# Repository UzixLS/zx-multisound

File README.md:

## ZX-MultiSound
Sound card for ZX Spectrum (NemoBus).

### Tech specs
* TurboSound FM (2xYM2203)
* General Sound (16MHz, 1024Kb of RAM)
* SAA1099 (use port #FF/#1FF to access SAA chip, write #F7/#FF to #FFFD port to enable/disable SAA)
* SounDrive (ports #0F, #1F, #4F, #5F)
* MIDI synthesizer (controlled via YM(AY) chip - compatible with ZX Spectrum 128K / ZXUNO)
* Low profile PCB: 170x64mm
* 5V and 12V power required
* 4x 1-bit digital DACs for GS and SounDrive

### Changelog & current status
* Rev.A - first release. Please note the [errata](pcb/rev.A/ERRATA.txt);
* Rev.A1 - fixed known rev.A issues. Please note the [errata](pcb/rev.A1/ERRATA.txt).
* Rev.A2:
    * Fixed Z80 clocking - added buffer;
    * Fixed 3.5mm jack footprint swapped left-right channels;
    * Fixed misplaced R20 and R34 labels on silkscreen;
    * 74LVC1G125DB replaced by 74AHCT1G125DB;
    * C3,C5,C17,C18 slightly moved left;
    * Added ledge on edge connector;
    * Improved SAM2695 footprint for hand soldering.
Sound card has been tested only with ZX Evolution. You can use it with another computer at your own risk.

### Related projects
* Turbo Sound FM - [link](http://www.nedopc.com/TURBOSOUND/ts-fm.php)
* ZXM-SoundCard - [link](http://micklab.ru/My%20Soundcard/ZXMSoundCard.htm)
* ZXM-GeneralSound - [link](http://micklab.ru/My%20Soundcard/ZXMGeneralSound.htm)
* NeoGS - [link](http://www.nedopc.com/gs/ngs.php)

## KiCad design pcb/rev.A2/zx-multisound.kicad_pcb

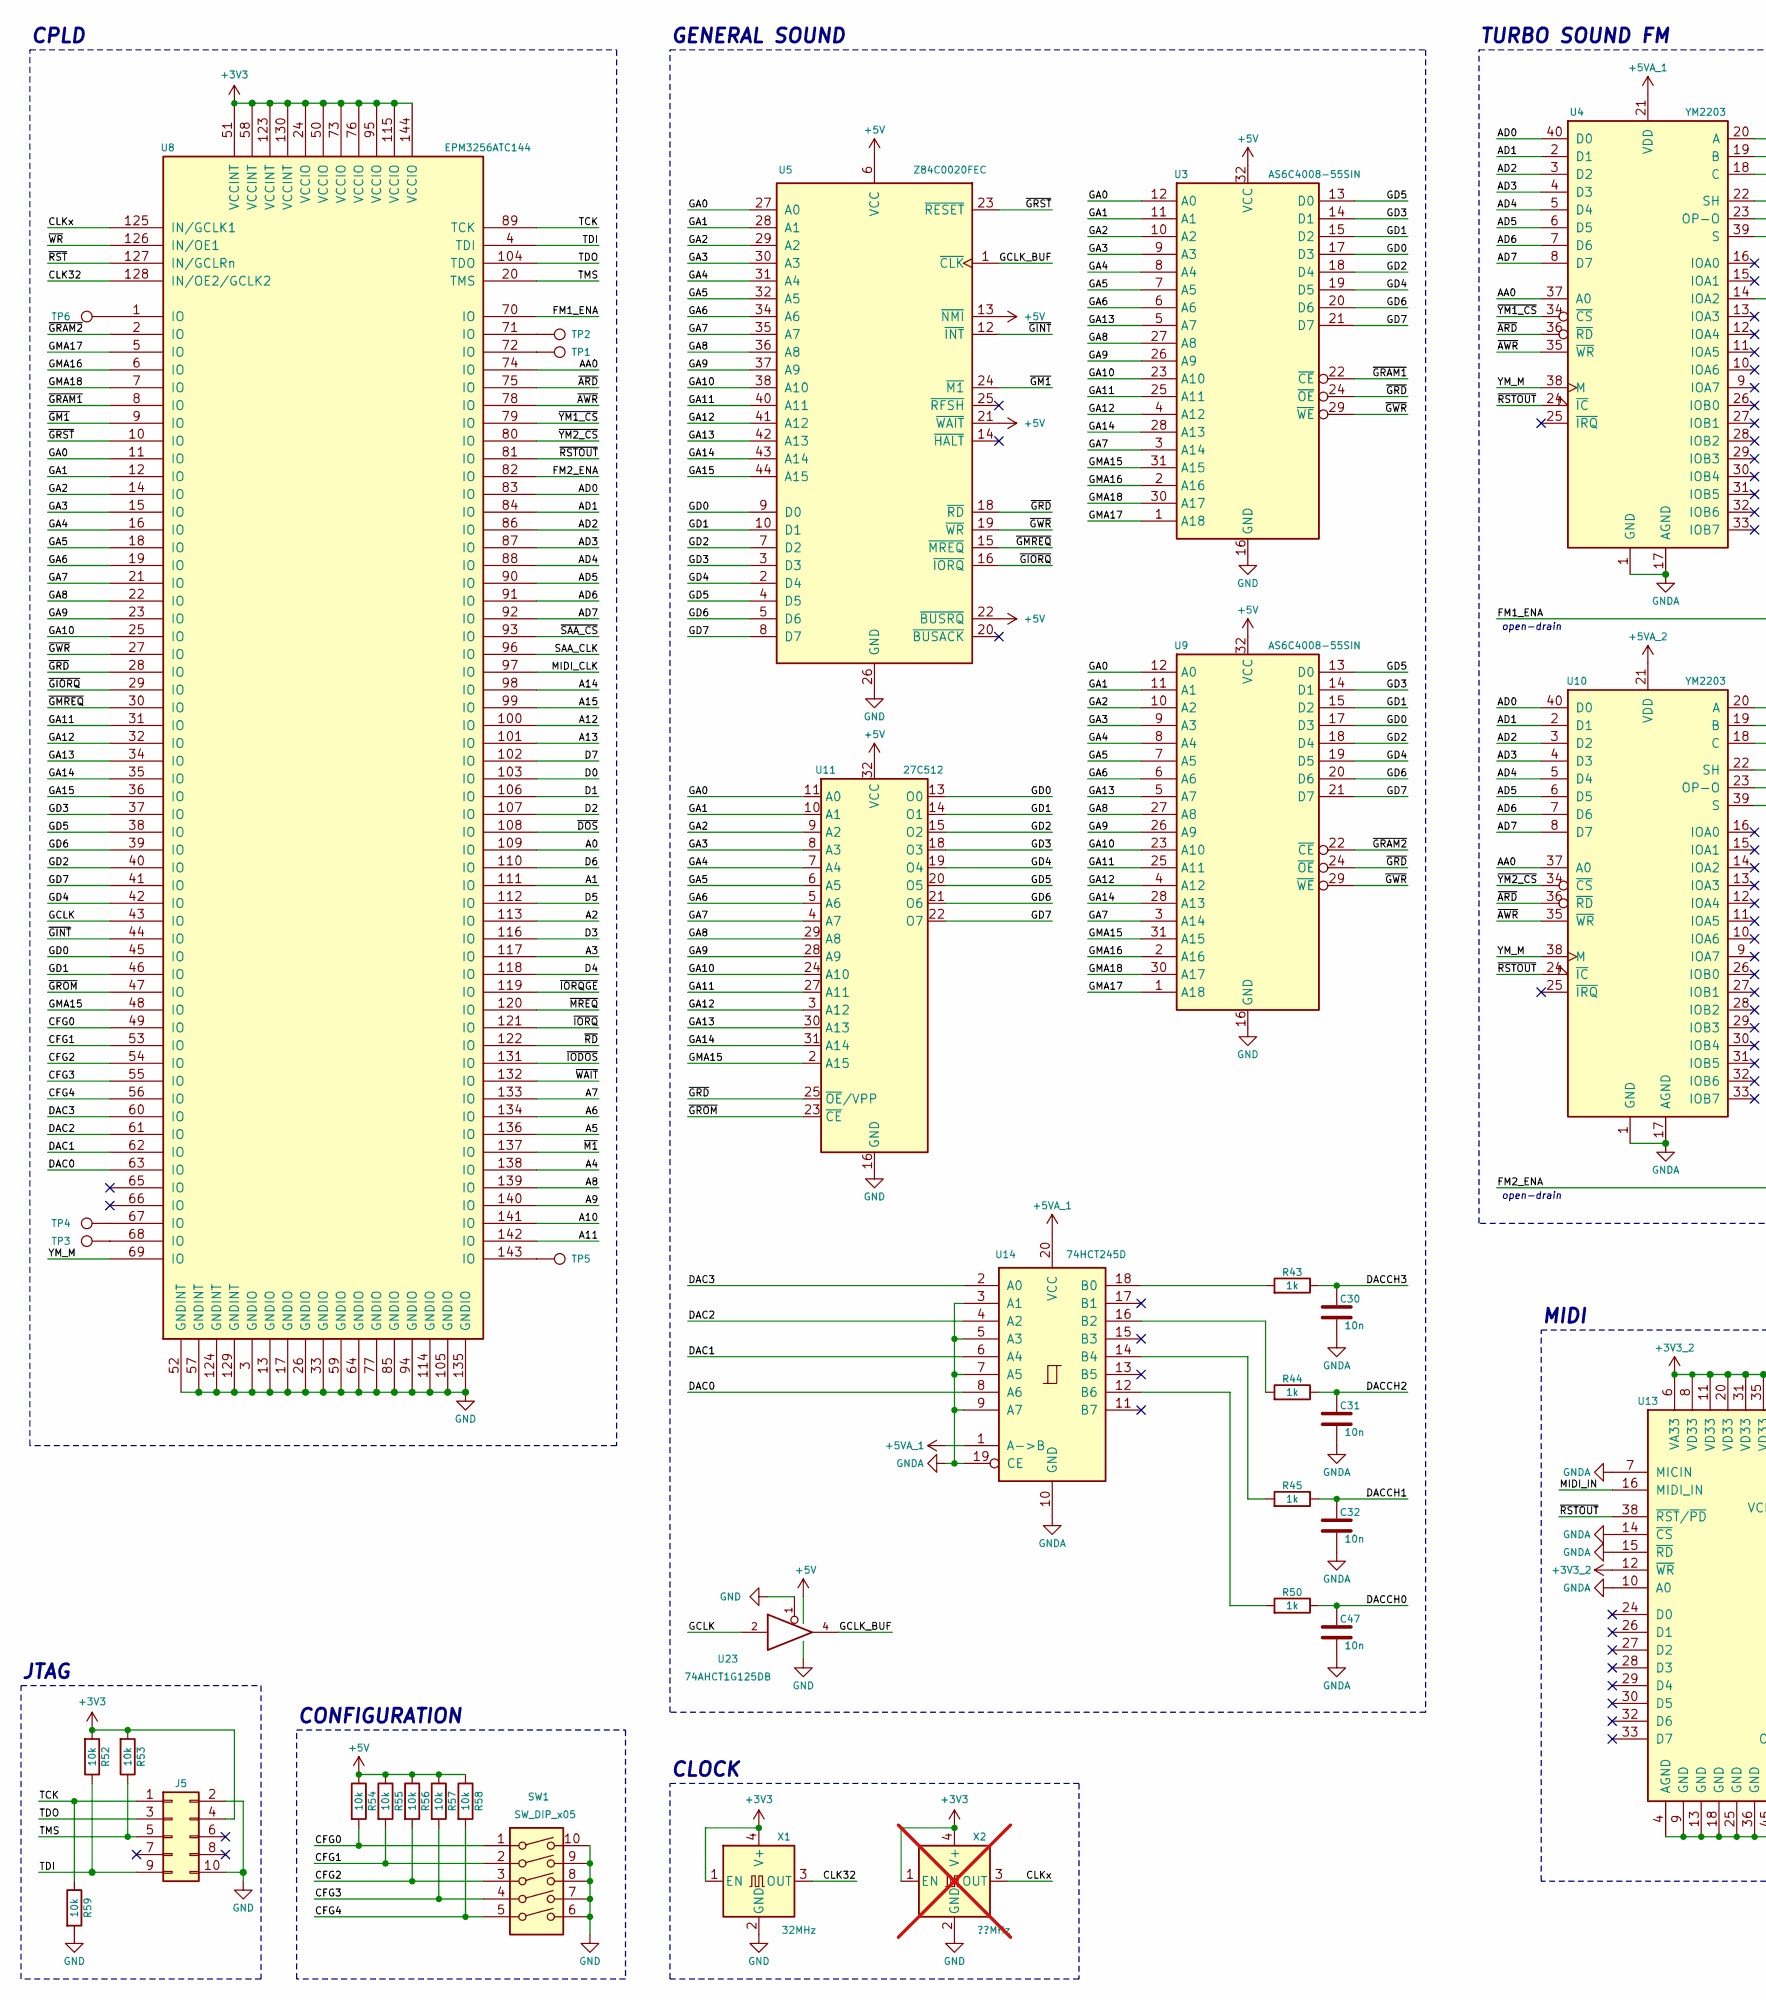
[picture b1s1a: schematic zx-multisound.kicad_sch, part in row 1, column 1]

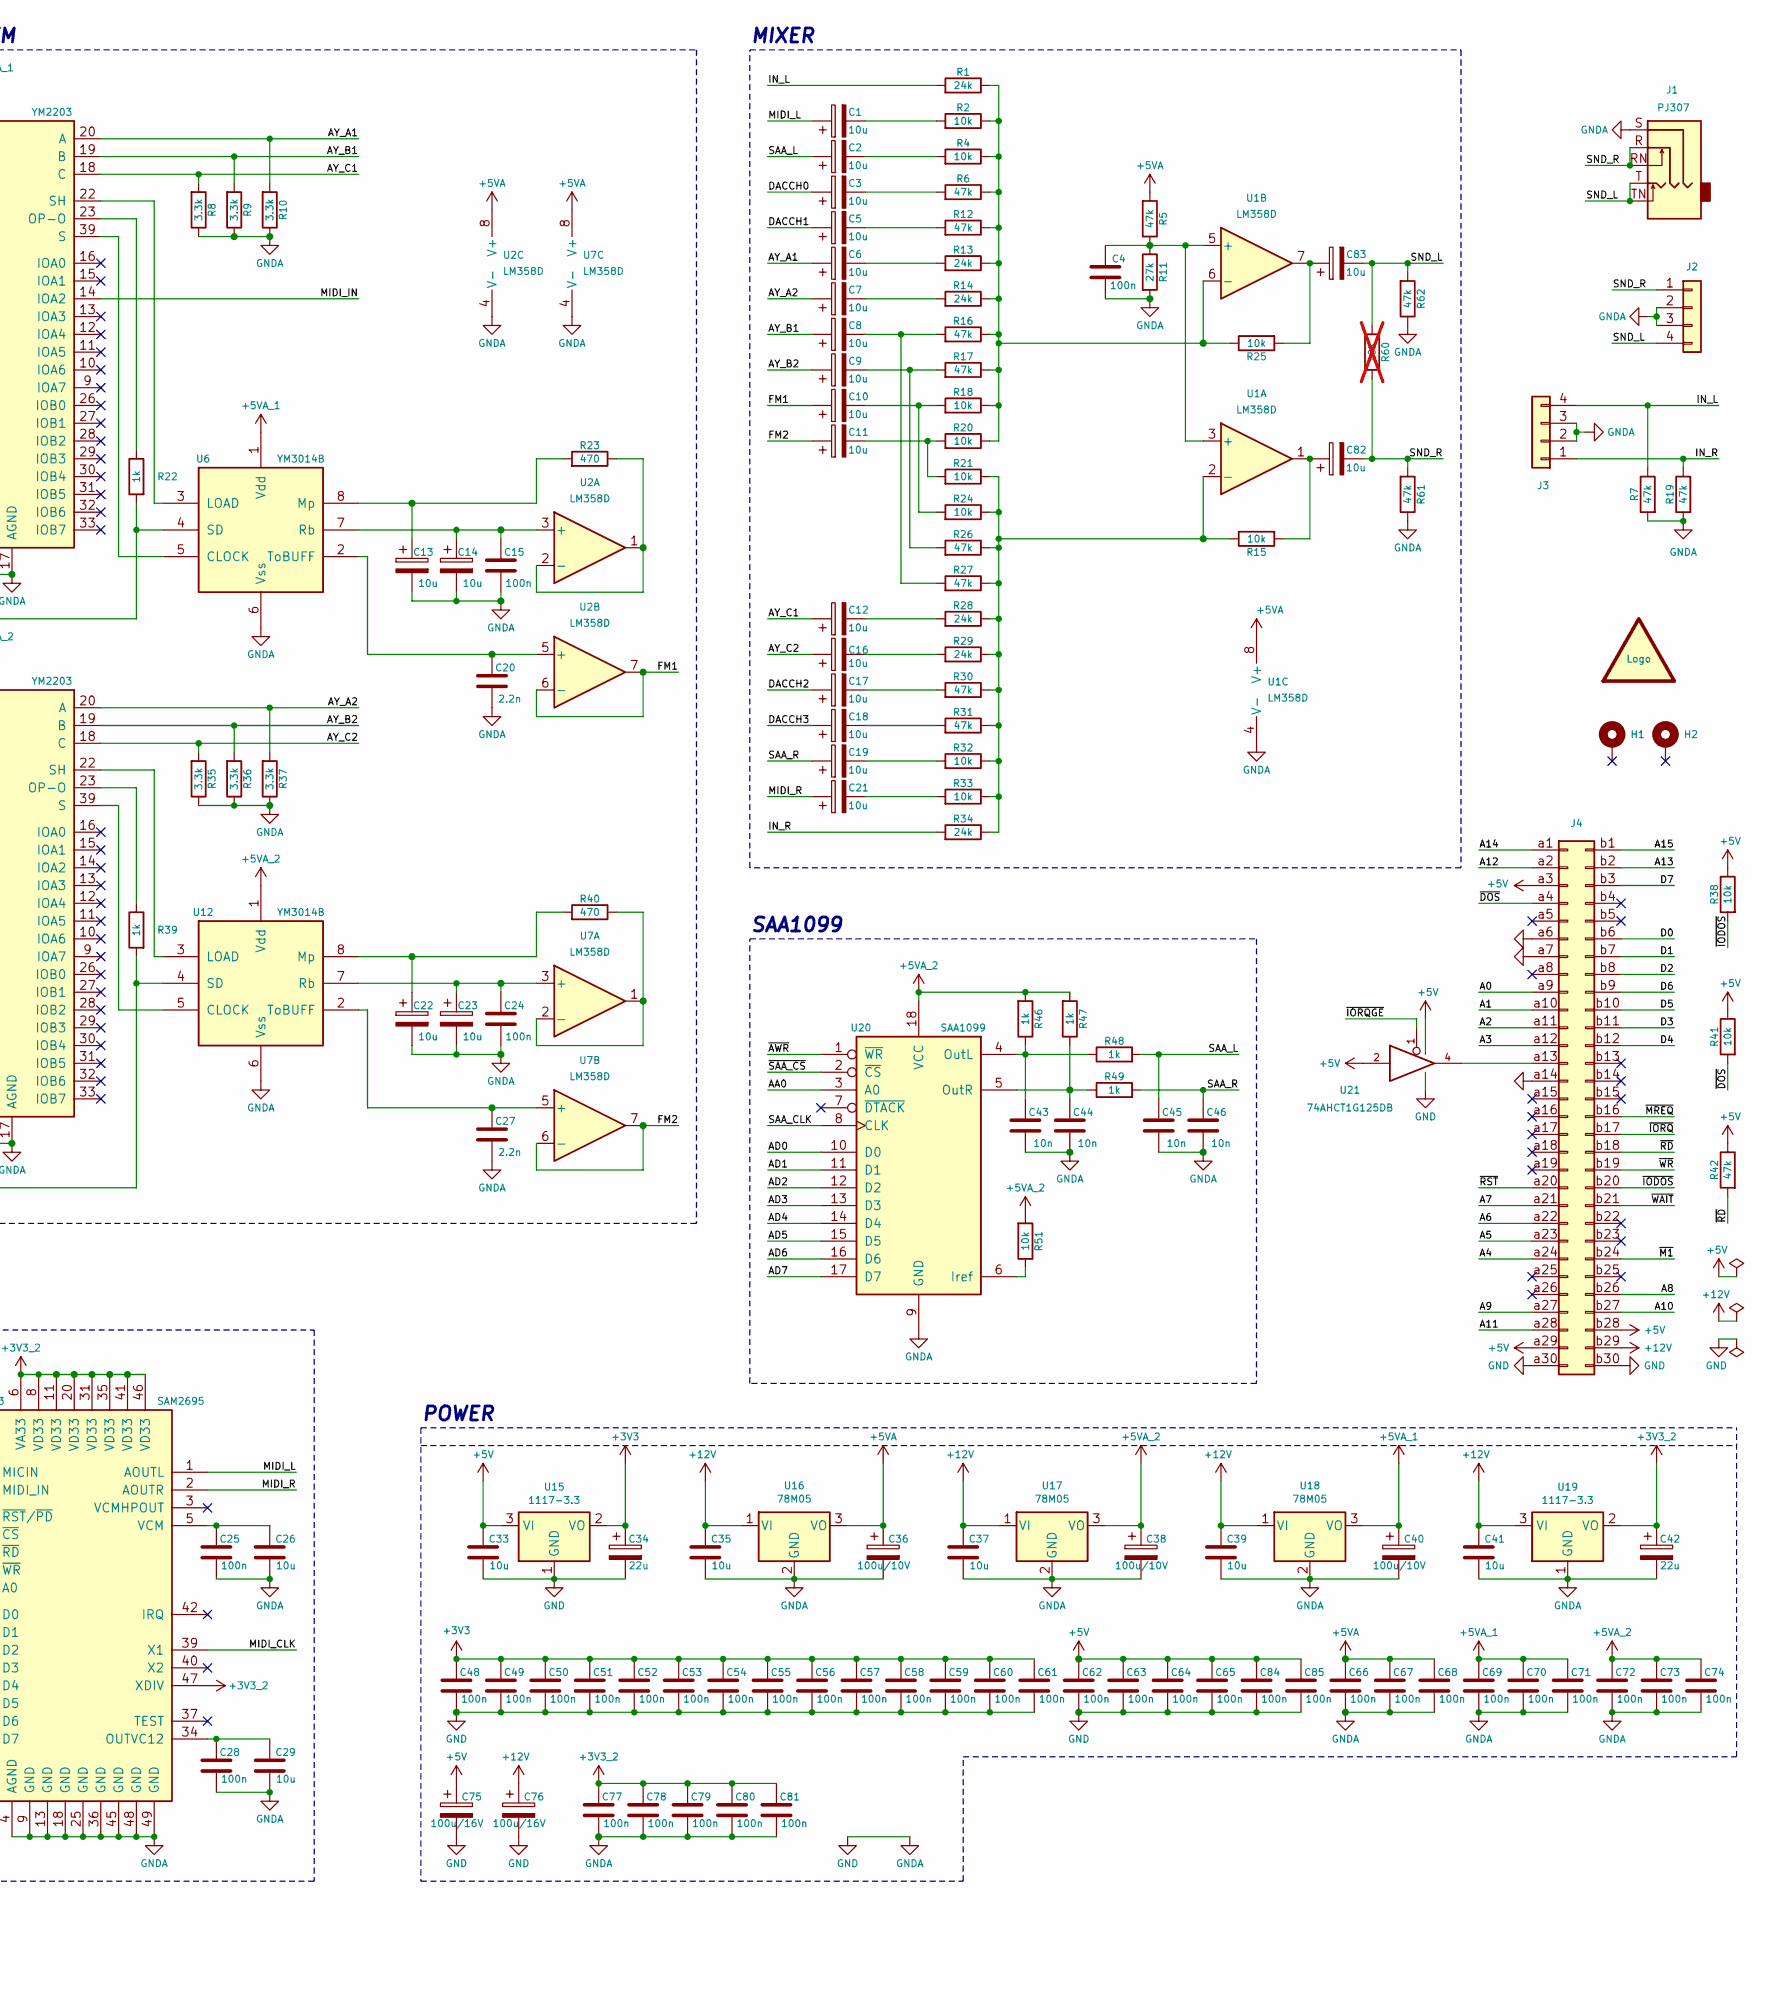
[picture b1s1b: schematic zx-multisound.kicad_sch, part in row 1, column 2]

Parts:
C1, C2, C3, C5, C6, C7, C8, C9, C10, C11, C12, C13, C14, C16, C17, C18, C19, C21, C22, C23, C82, C83: 10u; CP_Elec_4x5.4
C4, C15, C24, C25, C28, C48, C49, C50, C51, C52, C53, C54, C55, C56, C57, C58, C59, C60, C61, C62, C63, C64, C65, C66, C67, C68, C69, C70, C71, C72, C73, C74, C77, C78, C79, C80, C81, C84, C85: 100n; C_0805_2012Metric_Pad1.18x1.45mm_HandSolder
C20, C27: 2.2n; C_0805_2012Metric_Pad1.18x1.45mm_HandSolder
C26, C29, C33, C35, C37, C39, C41: 10u; C_1206_3216Metric_Pad1.33x1.80mm_HandSolder
C30, C31, C32, C43, C44, C45, C46, C47: 10n; C_0805_2012Metric_Pad1.18x1.45mm_HandSolder
C34, C42: 22u; CP_EIA-3216-18_Kemet-A_Pad1.58x1.35mm_HandSolder
C36, C38, C40: 100u/10V; CP_EIA-6032-28_Kemet-C_Pad2.25x2.35mm_HandSolder
C75, C76: 100u/16V; CP_Elec_6.3x7.7
H1, H2: MountingHole_Pad; MountingHole_2.7mm_M2.5_DIN965_Pad
J1: PJ307; PJ-307
J2, J3: Conn_01x04; PinHeader_1x04_P2.54mm_Vertical
J4: Conn_02x30_Row_Letter_First; ZX_NEMO_60_EDGE
J5: Conn_02x05_Odd_Even; PinHeader_2x05_P2.54mm_Vertical
LOGO1: graphic; black-mage-12.5x8.6
R1, R13, R14, R28, R29, R34: 24k; R_0805_2012Metric_Pad1.20x1.40mm_HandSolder
R2, R4, R15, R18, R20, R21, R24, R25, R32, R33, R38, R41, R51, R52, R53, R54, R55, R56, R57, R58, R59: 10k; R_0805_2012Metric_Pad1.20x1.40mm_HandSolder
R5, R6, R7, R12, R16, R17, R19, R26, R27, R30, R31, R42, R61, R62: 47k; R_0805_2012Metric_Pad1.20x1.40mm_HandSolder
R8, R9, R10, R35, R36, R37: 3.3k; R_0805_2012Metric_Pad1.20x1.40mm_HandSolder
R11: 27k; R_0805_2012Metric_Pad1.20x1.40mm_HandSolder
R22, R39, R43, R44, R45, R46, R47, R48, R49, R50: 1k; R_0805_2012Metric_Pad1.20x1.40mm_HandSolder
R23, R40: 470; R_0805_2012Metric_Pad1.20x1.40mm_HandSolder
R60: 10K; R_0805_2012Metric_Pad1.20x1.40mm_HandSolder; not fitted
SW1: SW_DIP_x05; SW_DIP_SPSTx05_Slide_6.7x14.26mm_W7.62mm_P2.54mm_LowProfile
TP1, TP2, TP3, TP4, TP5, TP6: TestPoint; TestPoint_Pad_D1.0mm
U1, U2, U7: LM358D; SOIC-8_3.9x4.9mm_P1.27mm
U3, U9: AS6C4008-55SIN; SSOP-32_11.305x20.495mm_P1.27mm
U4, U10: YM2203; DIP-40_W15.24mm_Socket
U5: Z84C0020FEC; TQFP-44_14x14mm_P0.8mm
U6, U12: YM3014B; DIP-8_W7.62mm_Socket
U8: EPM3256ATC144; TQFP-144_20x20mm_P0.5mm
U11: 27C512; PLCC-32_11.4x14.0mm_P1.27mm-longpads
U13: SAM2695; QFN-48-1EP_6x6mm_P0.4mm_EP4.2x4.2mm
U14: 74HCT245D; SOIC-20W_7.5x12.8mm_P1.27mm
U15, U19: 1117-3.3; SOT-223-3_TabPin2
U16, U17, U18: 78M05; TO-252-2
U20: SAA1099; DIP-18_W7.62mm_Socket
U21, U23: 74AHCT1G125DB; SOT-23-5_HandSoldering
X1: 32MHz; Oscillator_SMD_7050_7.0x5.0mm
X2: ??MHz; Oscillator_SMD_7050_7.0x5.0mm; not fitted

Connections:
+3V3: C34.1, C48.1, C49.1, C50.1, C51.1, C52.1, C53.1, C54.1, C55.1, C56.1, C57.1, C58.1, C59.1, C60.2, C61.2, J5.4, R52.2, R53.2, U8.24 (VCCIO), U8.50 (VCCIO), U8.51 (VCCINT), U8.58 (VCCINT), U8.73 (VCCIO), U8.76 (VCCIO), U8.95 (VCCIO), U8.115 (VCCIO), U8.123 (VCCINT), U8.130 (VCCINT), U8.144 (VCCIO), U15.2 (VO), X1.1 (EN), X1.4 (V+), X2.1 (EN), X2.4 (V+)
+3V3_2: C42.1, C77.1, C78.1, C79.1, C80.1, C81.1, U13.6 (VA33), U13.8 (VD33), U13.11 (VD33), U13.12 (~WR), U13.20 (VD33), U13.31 (VD33), U13.35 (VD33), U13.41 (VD33), U13.46 (VD33), U13.47 (XDIV), U19.2 (VO)
+5V: C33.1, C62.2, C63.2, C64.2, C65.2, C75.1, C84.2, C85.2, J4.a3, J4.a29, J4.b28, R38.1, R41.1, R42.1, R54.1, R55.1, R56.1, R57.1, R58.1, U3.32 (VCC), U5.6 (VCC), U5.13 (~NMI), U5.21 (~WAIT), U5.22 (~BUSRQ), U9.32 (VCC), U11.32 (VCC), U15.3 (VI), U21.2, U21.5 (VCC), U23.5 (VCC)
+5VA: C36.1, C66.2, C67.2, C68.2, R5.2, U1.8 (V+), U2.8 (V+), U7.8 (V+), U16.3 (VO)
+5VA_1: C40.1, C69.2, C70.2, C71.2, U4.21 (VDD), U6.1 (Vdd), U14.1 (A->B), U14.20 (VCC), U18.3 (VO)
+5VA_2: C38.1, C72.2, C73.2, C74.2, R46.2, R47.2, R51.2, U10.21 (VDD), U12.1 (Vdd), U17.3 (VO), U20.18 (VCC)
+12V: C35.1, C37.1, C39.1, C41.1, C76.1, J4.b29, U16.1 (VI), U17.1 (VI), U18.1 (VI), U19.3 (VI)
/A0: J4.a9, U8.109 (IO)
/A1: J4.a10, U8.111 (IO)
/A2: J4.a11, U8.113 (IO)
/A3: J4.a12, U8.117 (IO)
/A4: J4.a24, U8.138 (IO)
/A5: J4.a23, U8.136 (IO)
/A6: J4.a22, U8.134 (IO)
/A7: J4.a21, U8.133 (IO)
/A8: J4.b26, U8.139 (IO)
/A9: J4.a27, U8.140 (IO)
/A10: J4.b27, U8.141 (IO)
/A11: J4.a28, U8.142 (IO)
/A12: J4.a2, U8.100 (IO)
/A13: J4.b2, U8.101 (IO)
/A14: J4.a1, U8.98 (IO)
/A15: J4.b1, U8.99 (IO)
/AA0: U4.37 (A0), U8.74 (IO), U10.37 (A0), U20.3 (A0)
/AD0: U4.40 (D0), U8.83 (IO), U10.40 (D0), U20.10 (D0)
/AD1: U4.2 (D1), U8.84 (IO), U10.2 (D1), U20.11 (D1)
/AD2: U4.3 (D2), U8.86 (IO), U10.3 (D2), U20.12 (D2)
/AD3: U4.4 (D3), U8.87 (IO), U10.4 (D3), U20.13 (D3)
/AD4: U4.5 (D4), U8.88 (IO), U10.5 (D4), U20.14 (D4)
/AD5: U4.6 (D5), U8.90 (IO), U10.6 (D5), U20.15 (D5)
/AD6: U4.7 (D6), U8.91 (IO), U10.7 (D6), U20.16 (D6)
/AD7: U4.8 (D7), U8.92 (IO), U10.8 (D7), U20.17 (D7)
/AY_A1: C6.1, R10.2, U4.20 (A)
/AY_A2: C7.1, R37.2, U10.20 (A)
/AY_B1: C8.1, R9.2, U4.19 (B)
/AY_B2: C9.1, R36.2, U10.19 (B)
/AY_C1: C12.1, R8.2, U4.18 (C)
/AY_C2: C16.1, R35.2, U10.18 (C)
/CFG0: R54.2, SW1.1, U8.49 (IO)
/CFG1: R55.2, SW1.2, U8.53 (IO)
/CFG2: R56.2, SW1.3, U8.54 (IO)
/CFG3: R57.2, SW1.4, U8.55 (IO)
/CFG4: R58.2, SW1.5, U8.56 (IO)
/CLK32: U8.128 (IN/OE2/GCLK2), X1.3 (OUT)
/CLKx: U8.125 (IN/GCLK1), X2.3 (OUT)
/D0: J4.b6, U8.103 (IO)
/D1: J4.b7, U8.106 (IO)
/D2: J4.b8, U8.107 (IO)
/D3: J4.b11, U8.116 (IO)
/D4: J4.b12, U8.118 (IO)
/D5: J4.b10, U8.112 (IO)
/D6: J4.b9, U8.110 (IO)
/D7: J4.b3, U8.102 (IO)
/DAC0: U8.63 (IO), U14.8 (A6)
/DAC1: U8.62 (IO), U14.6 (A4)
/DAC2: U8.61 (IO), U14.4 (A2)
/DAC3: U8.60 (IO), U14.2 (A0)
/DACCH0: C3.1, C47.1, R50.1
/DACCH1: C5.1, C32.1, R45.1
/DACCH2: C17.1, C31.1, R44.1
/DACCH3: C18.1, C30.1, R43.1
/FM1: C10.1, U2.6 (-), U2.7
/FM1_ENA: R22.2, U6.4 (SD), U8.70 (IO)
/FM2: C11.1, U7.6 (-), U7.7
/FM2_ENA: R39.2, U8.82 (IO), U12.4 (SD)
/GA0: U3.12 (A0), U5.27 (A0), U8.11 (IO), U9.12 (A0), U11.11 (A0)
/GA1: U3.11 (A1), U5.28 (A1), U8.12 (IO), U9.11 (A1), U11.10 (A1)
/GA2: U3.10 (A2), U5.29 (A2), U8.14 (IO), U9.10 (A2), U11.9 (A2)
/GA3: U3.9 (A3), U5.30 (A3), U8.15 (IO), U9.9 (A3), U11.8 (A3)
/GA4: U3.8 (A4), U5.31 (A4), U8.16 (IO), U9.8 (A4), U11.7 (A4)
/GA5: U3.7 (A5), U5.32 (A5), U8.18 (IO), U9.7 (A5), U11.6 (A5)
/GA6: U3.6 (A6), U5.34 (A6), U8.19 (IO), U9.6 (A6), U11.5 (A6)
/GA7: U3.3 (A14), U5.35 (A7), U8.21 (IO), U9.3 (A14), U11.4 (A7)
/GA8: U3.27 (A8), U5.36 (A8), U8.22 (IO), U9.27 (A8), U11.29 (A8)
/GA9: U3.26 (A9), U5.37 (A9), U8.23 (IO), U9.26 (A9), U11.28 (A9)
/GA10: U3.23 (A10), U5.38 (A10), U8.25 (IO), U9.23 (A10), U11.24 (A10)
/GA11: U3.25 (A11), U5.40 (A11), U8.31 (IO), U9.25 (A11), U11.27 (A11)
/GA12: U3.4 (A12), U5.41 (A12), U8.32 (IO), U9.4 (A12), U11.3 (A12)
/GA13: U3.5 (A7), U5.42 (A13), U8.34 (IO), U9.5 (A7), U11.30 (A13)
/GA14: U3.28 (A13), U5.43 (A14), U8.35 (IO), U9.28 (A13), U11.31 (A14)
/GA15: U5.44 (A15), U8.36 (IO)
/GCLK: U8.43 (IO), U23.2
/GCLK_BUF: U5.1 (~CLK), U23.4
/GD0: U3.17 (D3), U5.9 (D0), U8.45 (IO), U9.17 (D3), U11.13 (O0)
/GD1: U3.15 (D2), U5.10 (D1), U8.46 (IO), U9.15 (D2), U11.14 (O1)
/GD2: U3.18 (D4), U5.7 (D2), U8.40 (IO), U9.18 (D4), U11.15 (O2)
/GD3: U3.14 (D1), U5.3 (D3), U8.37 (IO), U9.14 (D1), U11.18 (O3)
/GD4: U3.19 (D5), U5.2 (D4), U8.42 (IO), U9.19 (D5), U11.19 (O4)
/GD5: U3.13 (D0), U5.4 (D5), U8.38 (IO), U9.13 (D0), U11.20 (O5)
/GD6: U3.20 (D6), U5.5 (D6), U8.39 (IO), U9.20 (D6), U11.21 (O6)
/GD7: U3.21 (D7), U5.8 (D7), U8.41 (IO), U9.21 (D7), U11.22 (O7)
/GMA15: U3.31 (A15), U8.48 (IO), U9.31 (A15), U11.2 (A15)
/GMA16: U3.2 (A16), U8.6 (IO), U9.2 (A16)
/GMA17: U3.1 (A18), U8.5 (IO), U9.1 (A18)
/GMA18: U3.30 (A17), U8.7 (IO), U9.30 (A17)
/IN_L: J3.4, R1.2, R7.1
/IN_R: J3.1, R19.1, R34.2
/MIDI_CLK: U8.97 (IO), U13.39 (X1)
/MIDI_IN: U4.14 (IOA2), U13.16 (MIDI_IN)
/MIDI_L: C1.1, U13.1 (AOUTL)
/MIDI_R: C21.1, U13.2 (AOUTR)
/SAA_CLK: U8.96 (IO), U20.8 (CLK)
/SAA_L: C2.1, C45.1, R48.2
/SAA_R: C19.1, C46.1, R49.2
/SND_L: C83.2, J1.T, J1.TN, J2.4, R60.2, R62.2
/SND_R: C82.2, J1.R, J1.RN, J2.1, R60.1, R61.2
/TCK: J5.1, R59.1, U8.89 (TCK)
/TDI: J5.9, R52.1, U8.4 (TDI)
/TDO: J5.3, U8.104 (TDO)
/TMS: J5.5, R53.1, U8.20 (TMS)
/YM_M: U4.38 (M), U8.69 (IO), U10.38 (M)
/~ARD: U4.36 (~RD), U8.75 (IO), U10.36 (~RD)
/~AWR: U4.35 (~WR), U8.78 (IO), U10.35 (~WR), U20.1 (~WR)
/~DOS: J4.a4, R41.2, U8.108 (IO)
/~GINT: U5.12 (~INT), U8.44 (IO)
/~GIORQ: U5.16 (~IORQ), U8.29 (IO)
/~GM1: U5.24 (~M1), U8.9 (IO)
/~GMREQ: U5.15 (~MREQ), U8.30 (IO)
/~GRAM1: U3.22 (~CE), U8.8 (IO)
/~GRAM2: U8.2 (IO), U9.22 (~CE)
/~GRD: U3.24 (~OE), U5.18 (~RD), U8.28 (IO), U9.24 (~OE), U11.25 (~OE/VPP)
/~GROM: U8.47 (IO), U11.23 (~CE)
/~GRST: U5.23 (~RESET), U8.10 (IO)
/~GWR: U3.29 (~WE), U5.19 (~WR), U8.27 (IO), U9.29 (~WE)
/~IODOS: J4.b20, R38.2, U8.131 (IO)
/~IORQGE: U8.119 (IO), U21.1
/~IORQ: J4.b17, U8.121 (IO)
/~M1: J4.b24, U8.137 (IO)
/~MREQ: J4.b16, U8.120 (IO)
/~RD: J4.b18, R42.2, U8.122 (IO)
/~RSTOUT: U4.24 (~IC), U8.81 (IO), U10.24 (~IC), U13.38 (~RST/~PD)
/~RST: J4.a20, U8.127 (IN/GCLRn)
/~SAA_CS: U8.93 (IO), U20.2 (~CS)
/~WAIT: J4.b21, U8.132 (IO)
/~WR: J4.b19, U8.126 (IN/OE1)
/~YM1_CS: U4.34 (~CS), U8.79 (IO)
/~YM2_CS: U8.80 (IO), U10.34 (~CS)
GND: C4.1, C13.2, C14.2, C15.2, C20.2, C22.2, C23.2, C24.2, C25.2, C26.2, C27.2, C28.2, C29.2, C30.2, C31.2, C32.2, C33.2, C34.2, C35.2, C36.2, C37.2, C38.2, C39.2, C40.2, C41.2, C42.2, C43.2, C44.2, C45.2, C46.2, C47.2, C48.2, C49.2, C50.2, C51.2, C52.2, C53.2, C54.2, C55.2, C56.2, C57.2, C58.2, C59.2, C60.1, C61.1, C62.1, C63.1, C64.1, C65.1, C66.1, C67.1, C68.1, C69.1, C70.1, C71.1, C72.1, C73.1, C74.1, C75.2, C76.2, C77.2, C78.2, C79.2, C80.2, C81.2, C84.1, C85.1, J1.S, J2.2, J2.3, J3.2, J3.3, J4.a6, J4.a7, J4.a14, J4.a30, J4.b30, J5.2, J5.10, R7.2, R8.1, R9.1, R10.1, R11.2, R19.2, R35.1, R36.1, R37.1, R59.2, R61.1, R62.1, SW1.6, SW1.7, SW1.8, SW1.9, SW1.10, U1.4 (V-), U2.4 (V-), U3.16 (GND), U4.1 (GND), U4.17 (AGND), U5.26 (GND), U6.6 (Vss), U7.4 (V-), U8.3 (GNDIO), U8.13 (GNDIO), U8.17 (GNDIO), U8.26 (GNDIO), U8.33 (GNDIO), U8.52 (GNDINT), U8.57 (GNDINT), U8.59 (GNDIO), U8.64 (GNDIO), U8.77 (GNDIO), U8.85 (GNDIO), U8.94 (GNDIO), U8.105 (GNDIO), U8.114 (GNDIO), U8.124 (GNDINT), U8.129 (GNDINT), U8.135 (GNDIO), U9.16 (GND), U10.1 (GND), U10.17 (AGND), U11.16 (GND), U12.6 (Vss), U13.4 (AGND), U13.7 (MICIN), U13.9 (GND), U13.10 (A0), U13.13 (GND), U13.14 (~CS), U13.15 (~RD), U13.18 (GND), U13.25 (GND), U13.36 (GND), U13.45 (GND), U13.48 (GND), U13.49 (GND), U14.3 (A1), U14.5 (A3), U14.7 (A5), U14.9 (A7), U14.10 (GND), U14.19 (CE), U15.1 (GND), U16.2 (GND), U17.2 (GND), U18.2 (GND), U19.1 (GND), U20.9 (GND), U21.3 (GND), U23.1, U23.3 (GND), X1.2 (GND), X2.2 (GND)
unnamed: C1.2, R2.2
unnamed: C2.2, R4.2
unnamed: C3.2, R6.2
unnamed: C5.2, R12.2
unnamed: C6.2, R13.2
unnamed: C7.2, R14.2
unnamed: C8.2, R16.2, R27.2
unnamed: C9.2, R17.2, R26.2
unnamed: C10.2, R18.2, R24.2
unnamed: C11.2, R20.2, R21.2
unnamed: C12.2, R28.2
unnamed: C16.2, R29.2
unnamed: C17.2, R30.2
unnamed: C18.2, R31.2
unnamed: C19.2, R32.2
unnamed: C21.2, R33.2
unnamed: C82.1, R15.2, U1.1
unnamed: C83.1, R25.2, U1.7
unnamed: J4.a13, U21.4
unnamed: TP1.1, U8.72 (IO)
unnamed: TP2.1, U8.71 (IO)
unnamed: TP3.1, U8.68 (IO)
unnamed: TP4.1, U8.67 (IO)
unnamed: TP5.1, U8.143 (IO)
unnamed: TP6.1, U8.1 (IO)
unnamed: C4.2, R5.1, R11.1, U1.3 (+), U1.5 (+)
unnamed: R15.1, R21.1, R24.1, R26.1, R27.1, R28.1, R29.1, R30.1, R31.1, R32.1, R33.1, R34.1, U1.2 (-)
unnamed: R1.1, R2.1, R4.1, R6.1, R12.1, R13.1, R14.1, R16.1, R17.1, R18.1, R20.1, R25.1, U1.6 (-)
unnamed: C14.1, C15.1, U2.3 (+), U6.7 (Rb)
unnamed: R23.1, U2.1, U2.2 (-)
unnamed: C20.1, U2.5 (+), U6.2 (ToBUFF)
unnamed: R22.1, U4.23 (OP-O)
unnamed: U4.39 (S), U6.5 (CLOCK)
unnamed: U4.22 (SH), U6.3 (LOAD)
unnamed: C13.1, R23.2, U6.8 (Mp)
unnamed: R40.1, U7.1, U7.2 (-)
unnamed: R39.1, U10.23 (OP-O)
unnamed: U10.39 (S), U12.5 (CLOCK)
unnamed: U10.22 (SH), U12.3 (LOAD)
unnamed: C22.1, R40.2, U12.8 (Mp)
unnamed: C23.1, C24.1, U7.3 (+), U12.7 (Rb)
unnamed: C27.1, U7.5 (+), U12.2 (ToBUFF)
unnamed: C28.1, C29.1, U13.34 (OUTVC12)
unnamed: C25.1, C26.1, U13.5 (VCM)
unnamed: R43.2, U14.18 (B0)
unnamed: R44.2, U14.16 (B2)
unnamed: R45.2, U14.14 (B4)
unnamed: R50.2, U14.12 (B6)
unnamed: R51.1, U20.6 (Iref)
unnamed: C43.1, R46.1, R48.1, U20.4 (OutL)
unnamed: C44.1, R47.1, R49.1, U20.5 (OutR)

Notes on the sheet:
SAA1099
CONFIGURATION
open-drain
GENERAL SOUND
TURBO SOUND FM
MIXER
CPLD
JTAG
POWER
MIDI
CLOCK

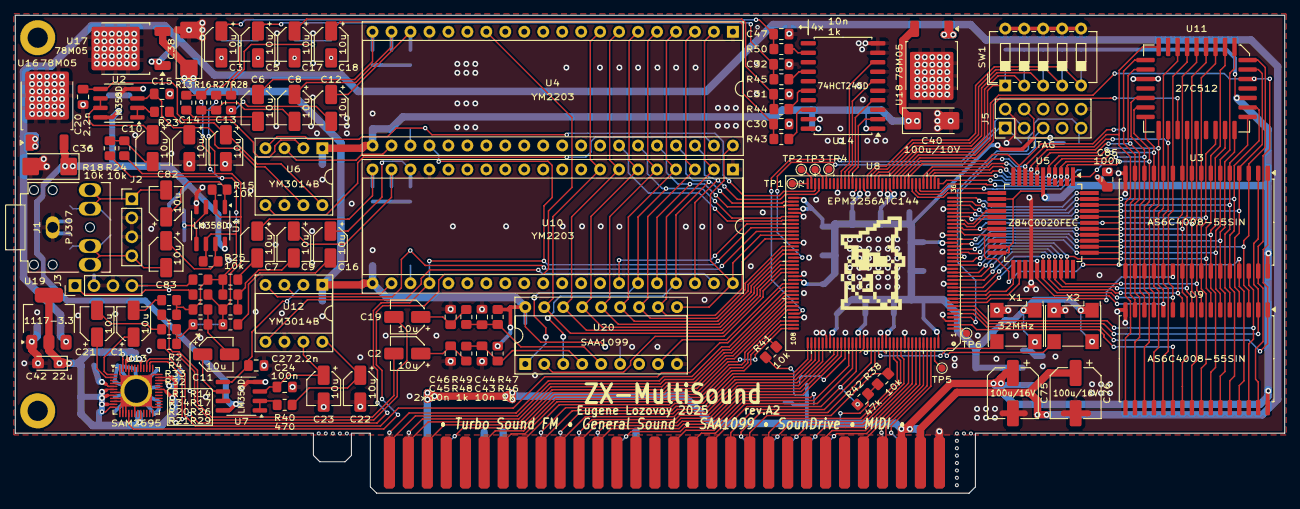
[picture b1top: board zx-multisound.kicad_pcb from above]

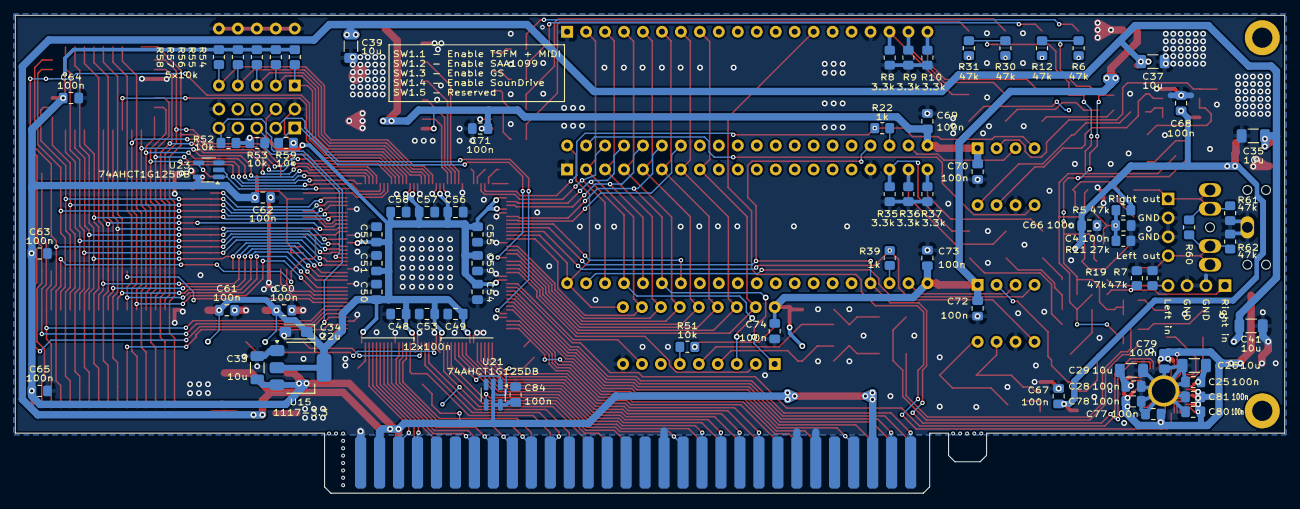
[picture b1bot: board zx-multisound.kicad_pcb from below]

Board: 2 copper layers, 170.0 x 64.0 mm, 185 parts (75 on the bottom side), 189 nets.
